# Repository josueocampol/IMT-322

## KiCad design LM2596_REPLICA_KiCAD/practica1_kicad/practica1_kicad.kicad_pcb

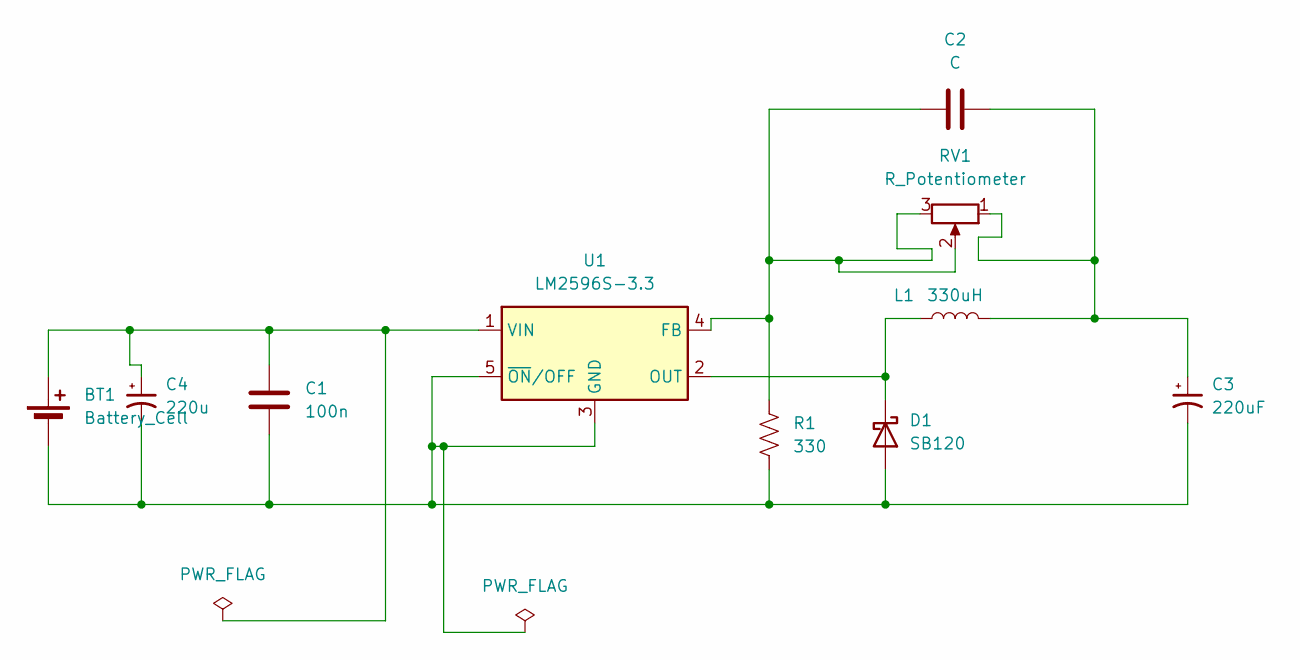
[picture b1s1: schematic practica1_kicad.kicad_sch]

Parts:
BT1: Battery_Cell; BatteryHolder_Keystone_2460_1xAA
C1: 100n; C_1210_3225Metric
C2: C; C_0402_1005Metric_Pad0.74x0.62mm_HandSolder
C3: 220uF; CP_Elec_3x5.4
C4: 220u; CP_Elec_3x5.4
D1: SB120; D_DO-41_SOD81_P10.16mm_Horizontal
L1: 330uH; L_7.3x7.3_H4.5
R1: 330; R_0402_1005Metric_Pad0.72x0.64mm_HandSolder
RV1: R_Potentiometer; Potentiometer_ACP_CA9-VSMD_Vertical_Hole
U1: LM2596S-3.3; TO-263-5_TabPin3

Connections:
unnamed: BT1.1 (+), C1.1, C4.1, U1.1 (VIN)
unnamed: BT1.2 (-), C1.2, C3.2, C4.2, D1.2 (A), R1.2, U1.3 (GND), U1.5 (~ON/OFF)
unnamed: C2.2, C3.1, L1.2, RV1.1
unnamed: D1.1 (K), L1.1, U1.2 (OUT)
unnamed: C2.1, R1.1, RV1.2, RV1.3, U1.4 (FB)

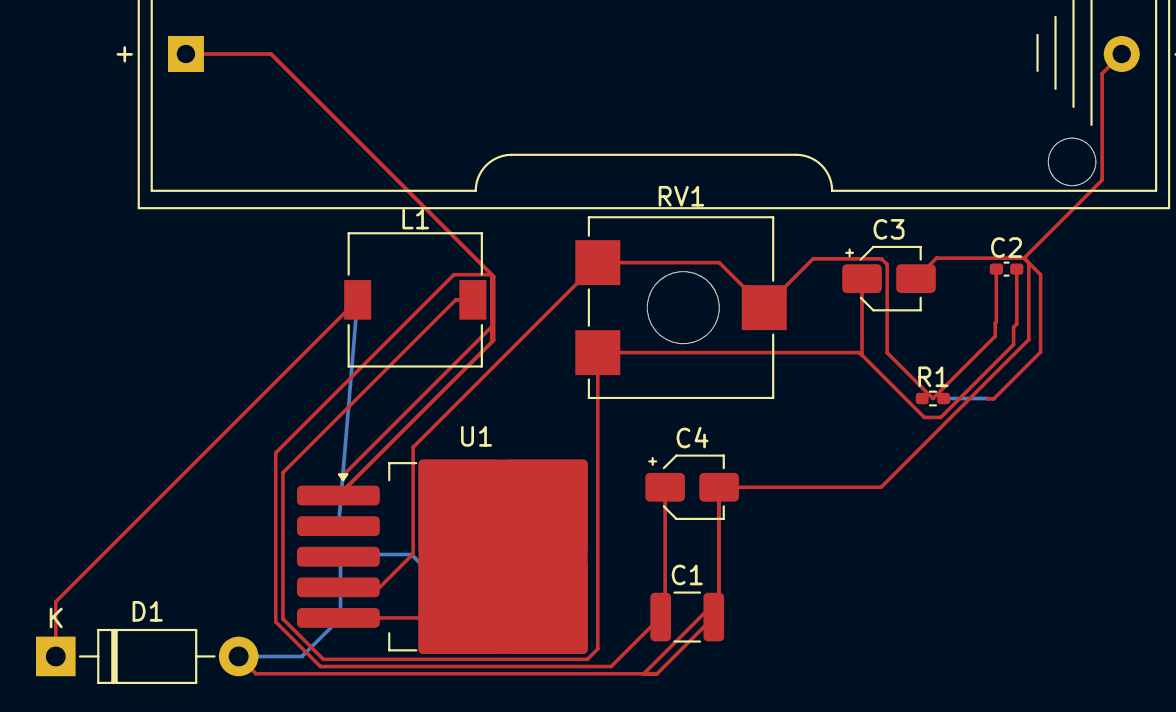
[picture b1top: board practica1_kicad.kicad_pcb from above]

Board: 2 copper layers, 10 parts (0 on the bottom side), 5 nets.

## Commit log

2024-02-17 Update README.md
    name
2024-02-17 prueba1
2024-02-17 prueba2
2024-02-24 P1 punto2
2024-03-02 Practica2
2024-03-02 Practica2punto2
2024-03-09 Cambio PUNTO 2
2024-03-19 Punto 1
2024-03-19 Examen
2024-04-07 PCB en KiCAD
2024-04-19 practica en clase
2024-04-19 FSM Semaforo
2024-04-19 Ultrasonico
2024-04-20 actualización archivos kicad
2024-04-20 Desarrollo de modulo NRF24L01 2.4GHz
2024-04-23 practica_elevador
2024-04-27 Prueba de Laboratorio 2
2024-04-27 Últimas Correcciones Examen laboratorio 2
2024-05-18 Blink Cortex A
2024-05-20 recuperatorio
2024-05-20 diagrama FSM agregado
